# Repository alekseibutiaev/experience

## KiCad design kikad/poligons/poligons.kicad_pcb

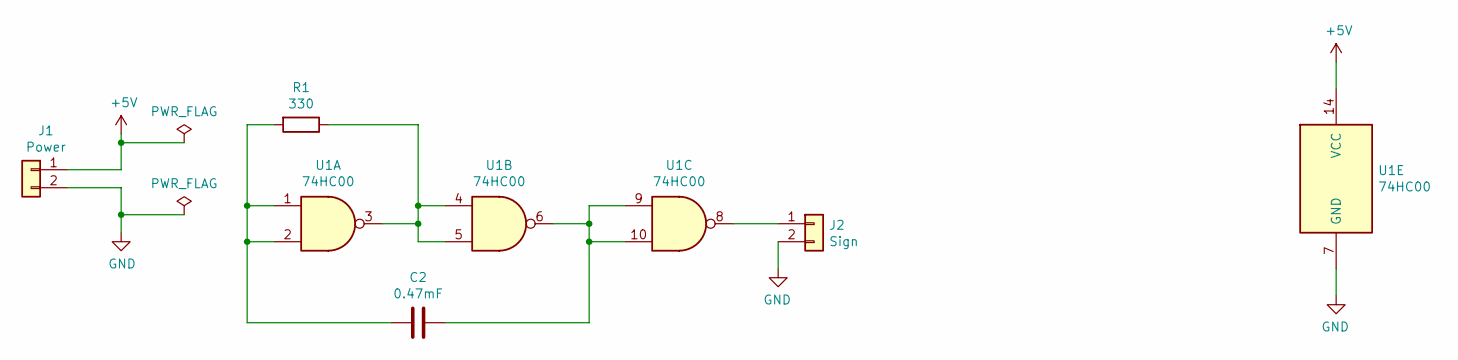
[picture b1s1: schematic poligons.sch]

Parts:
C2: 0.47mF; C_Axial_L3.8mm_D2.6mm_P7.50mm_Horizontal
J1: Power; PinHeader_1x02_P2.54mm_Vertical
J2: Sign; PinHeader_1x02_P2.54mm_Vertical
R1: 330; R_Axial_DIN0411_L9.9mm_D3.6mm_P15.24mm_Horizontal
U1: 74HC00; SO-14_3.9x8.65mm_P1.27mm

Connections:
+5V: J1.1, U1.14 (VCC)
GND: J1.2, J2.2, U1.7 (GND)
unnamed: C2.1, U1.6, U1.9, U1.10
unnamed: C2.2, R1.2, U1.1, U1.2
unnamed: J2.1, U1.8
unnamed: R1.1, U1.3, U1.4, U1.5

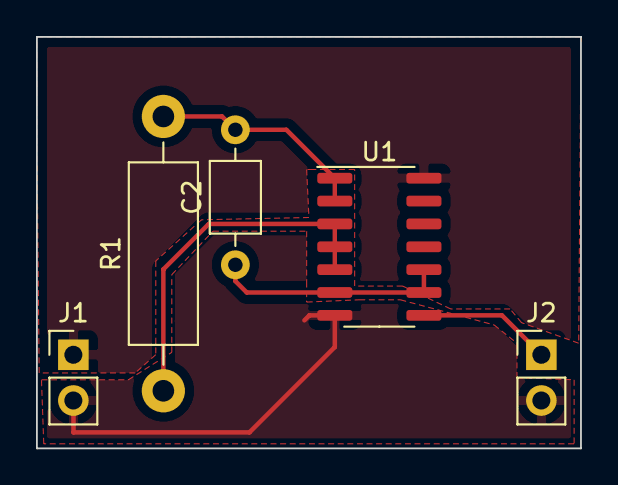
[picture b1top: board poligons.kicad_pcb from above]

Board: 2 copper layers, 30.2 x 22.9 mm, 5 parts (0 on the bottom side), 6 nets.

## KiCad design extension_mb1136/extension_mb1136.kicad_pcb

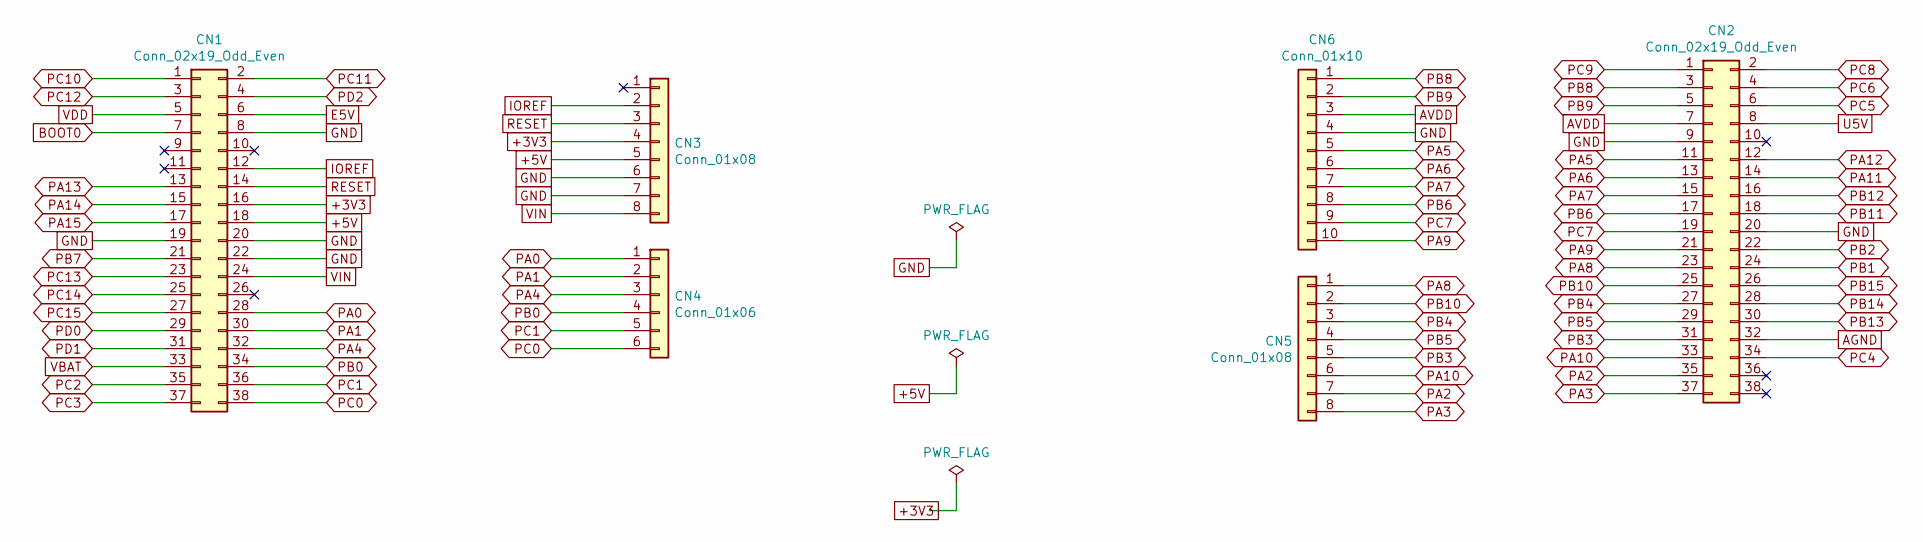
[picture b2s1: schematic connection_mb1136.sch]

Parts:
CN1, CN2: Conn_02x19_Odd_Even; PinHeader_2x19_P2.54mm_Vertical
CN3, CN5: Conn_01x08; PinSocket_1x08_P2.54mm_Vertical
CN4: Conn_01x06; PinSocket_1x06_P2.54mm_Vertical
CN6: Conn_01x10; PinSocket_1x10_P2.54mm_Vertical

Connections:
+3V3: CN1.16, CN3.4; also elsewhere on the board
+5V: CN1.18, CN3.5; also elsewhere on the board
AGND: CN2.32
AVDD: CN2.7, CN6.3
BOOT0: CN1.7
E5V: CN1.6
GND: CN1.8, CN1.19, CN1.20, CN1.22, CN2.9, CN2.20, CN3.6, CN3.7, CN6.4; also elsewhere on the board
IOREF: CN1.12, CN3.2
PA0: CN1.28, CN4.1
PA1: CN1.30, CN4.2
PA2: CN2.35, CN5.7
PA3: CN2.37, CN5.8
PA4: CN1.32, CN4.3
PA5: CN2.11, CN6.5
PA6: CN2.13, CN6.6
PA7: CN2.15, CN6.7
PA8: CN2.23, CN5.1
PA9: CN2.21, CN6.10; also elsewhere on the board
PA10: CN2.33, CN5.6
PA11: CN2.14; also elsewhere on the board
PA12: CN2.12; also elsewhere on the board
PA13: CN1.13
PA14: CN1.15
PA15: CN1.17
PB0: CN1.34, CN4.4
PB1: CN2.24
PB2: CN2.22
PB3: CN2.31, CN5.5
PB4: CN2.27, CN5.3
PB5: CN2.29, CN5.4
PB6: CN2.17, CN6.8
PB7: CN1.21
PB8: CN2.3, CN6.1
PB9: CN2.5, CN6.2
PB10: CN2.25, CN5.2; also elsewhere on the board
PB11: CN2.18
PB12: CN2.16
PB13: CN2.30
PB14: CN2.28
PB15: CN2.26
PC0: CN1.38, CN4.6
PC1: CN1.36, CN4.5
PC2: CN1.35
PC3: CN1.37
PC4: CN2.34
PC5: CN2.6
PC6: CN2.4
PC7: CN2.19, CN6.9
PC8: CN2.2; also elsewhere on the board
PC9: CN2.1; also elsewhere on the board
PC10: CN1.1
PC11: CN1.2
PC12: CN1.3
PC13: CN1.23
PC14: CN1.25
PC15: CN1.27
PD0: CN1.29
PD1: CN1.31
PD2: CN1.4
RESET: CN1.14, CN3.3
U5V: CN2.8
VBAT: CN1.33
VDD: CN1.5
VIN: CN1.24, CN3.8

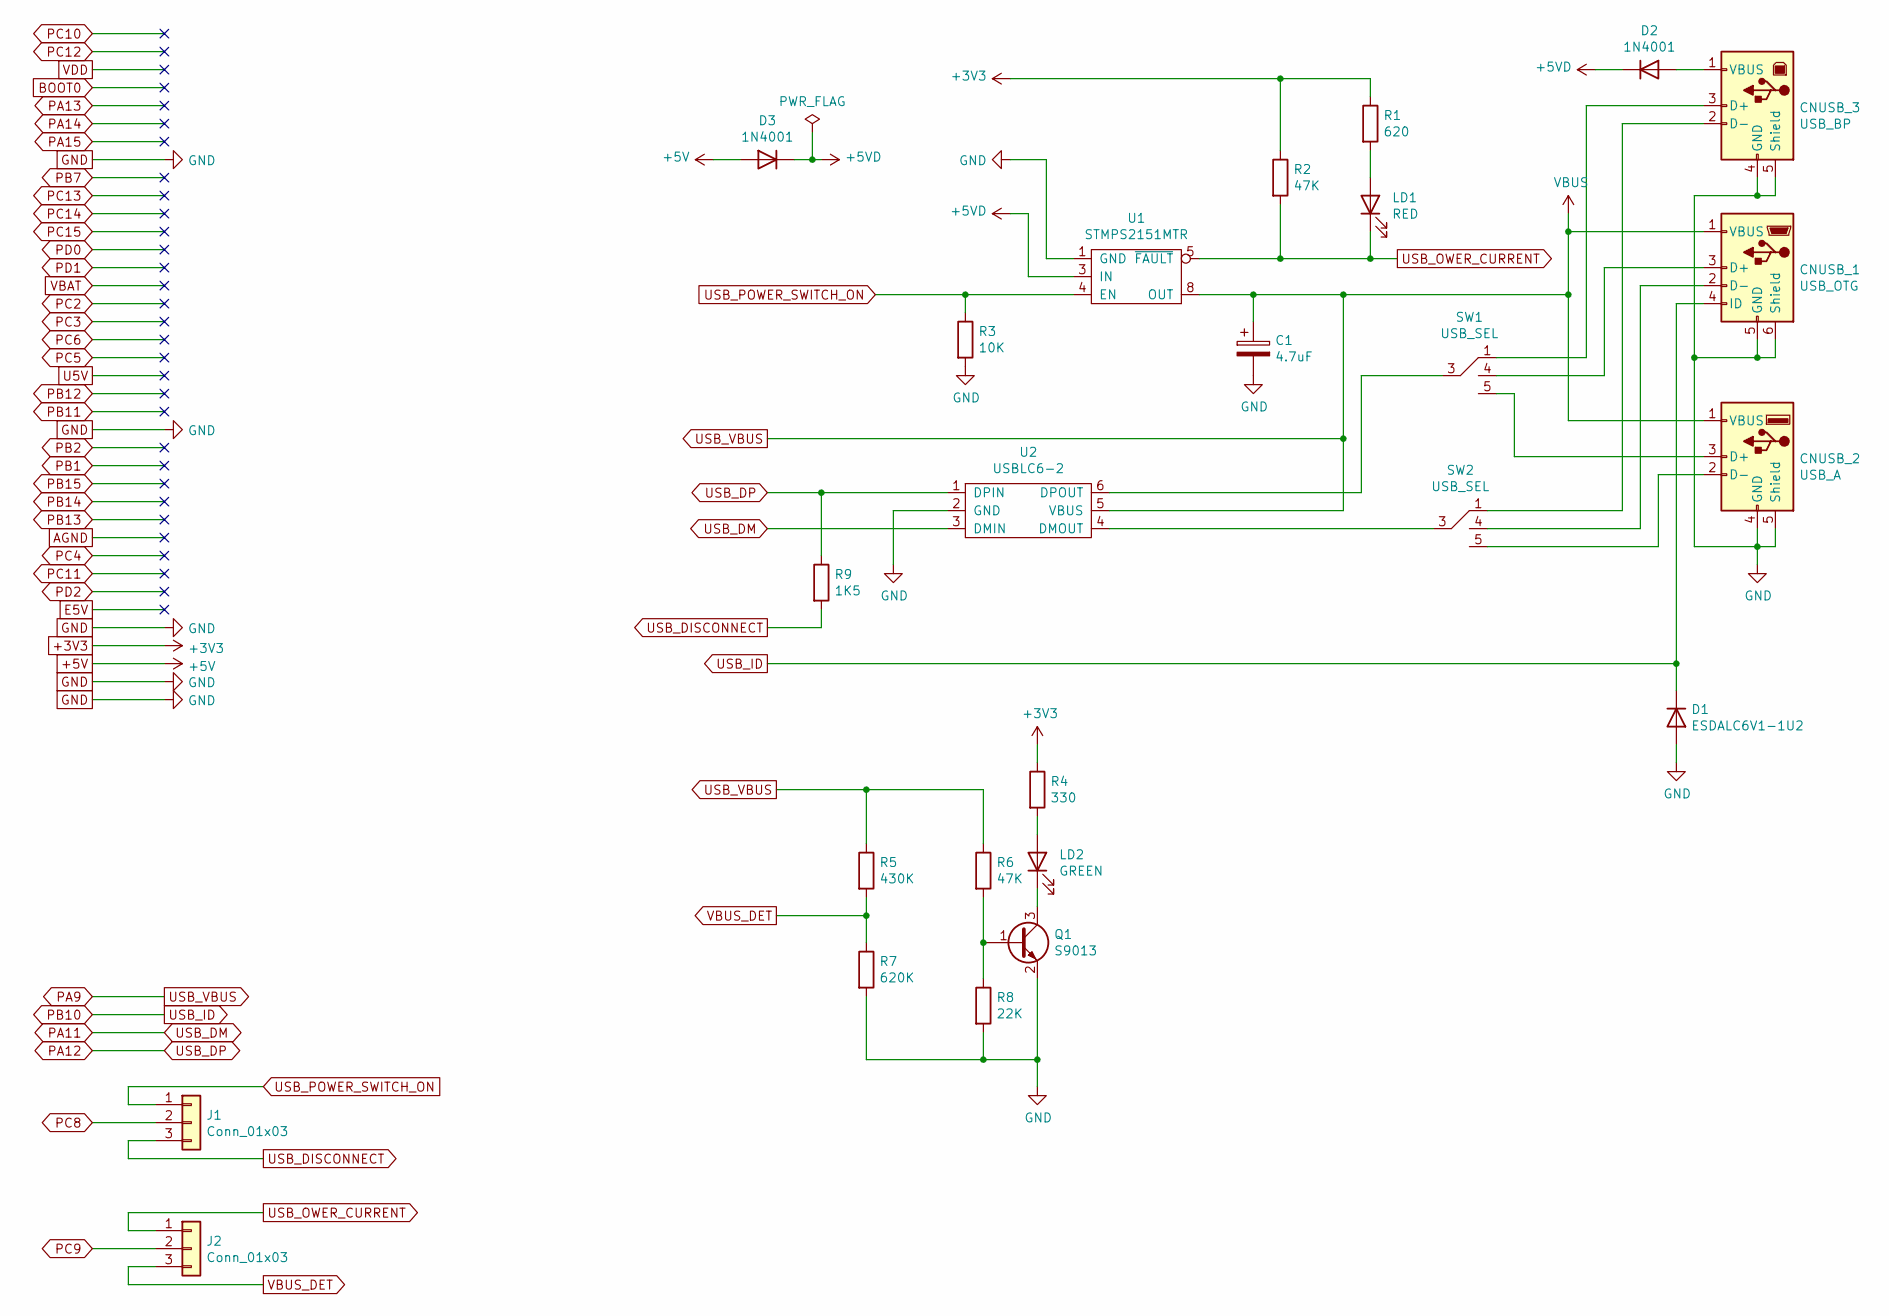
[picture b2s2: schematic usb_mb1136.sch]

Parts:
C1: 4.7uF; C_1206_3216Metric_Pad1.33x1.80mm_HandSolder
CNUSB_1: USB_OTG; USB_Micro-B_Molex-105017-0001
CNUSB_2: USB_A; USB_A_Molex_67643_Horizontal
CNUSB_3: USB_BP; USB_B_OST_USB-B1HSxx_Horizontal
D1: ESDALC6V1-1U2; D_0201_0603Metric
D2, D3: 1N4001; D_SOD-323_HandSoldering
J1, J2: Conn_01x03; PinHeader_1x03_P2.54mm_Vertical
LD1: RED; D_0805_2012Metric
LD2: GREEN; D_0805_2012Metric
Q1: S9013; SOT-23
R1: 620; R_0805_2012Metric
R2, R6: 47K; R_0805_2012Metric
R3: 10K; R_0805_2012Metric
R4: 330; R_0805_2012Metric
R5: 430K; R_0805_2012Metric
R7: 620K; R_0805_2012Metric
R8: 22K; R_0805_2012Metric
R9: 1K5; R_0805_2012Metric
SW1, SW2: USB_SEL; PinHeader_2x03_P2.54mm_Vertical
U1: STMPS2151MTR; SO-8_3.9x4.9mm_P1.27mm
U2: USBLC6-2; SOT-23-6_Handsoldering

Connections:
+3V3: R1.1, R2.1, R4.1; also elsewhere on the board
+5V: D3.2 (A); also elsewhere on the board
+5VD: D2.1 (K), D3.1 (K), U1.2 (IN), U1.3 (IN)
GND: C1.2, CNUSB_1.5 (GND), CNUSB_1.6 (Shield), CNUSB_2.4 (GND), CNUSB_2.5 (Shield), CNUSB_3.4 (GND), CNUSB_3.5 (Shield), D1.2 (A), Q1.2 (E), R3.2, R7.2, R8.2, U1.1 (GND), U2.2 (GND); also elsewhere on the board
unnamed: CNUSB_1.2 (D-), SW2.4
unnamed: CNUSB_1.3 (D+), SW1.4
unnamed: CNUSB_2.2 (D-), SW2.5
unnamed: CNUSB_2.3 (D+), SW1.5
unnamed: CNUSB_3.1 (VBUS), D2.2 (A)
unnamed: CNUSB_3.2 (D-), SW2.1
unnamed: CNUSB_3.3 (D+), SW1.1
unnamed: LD1.2 (A), R1.2
unnamed: LD2.1 (K), Q1.3 (C)
unnamed: LD2.2 (A), R4.2
unnamed: Q1.1 (B), R6.2, R8.1
unnamed: SW1.3, U2.6 (DPOUT)
unnamed: SW2.3, U2.4 (DMOUT)
PA9: C1.1, CNUSB_1.1 (VBUS), CNUSB_2.1 (VBUS), R5.1, R6.1, U1.6 (OUT), U1.7 (OUT), U1.8 (OUT), U2.5 (VBUS); also elsewhere on the board
PA11: U2.3 (DMIN); also elsewhere on the board
PA12: R9.1, U2.1 (DPIN); also elsewhere on the board
PB10: CNUSB_1.4 (ID), D1.1 (K); also elsewhere on the board
PC8: J1.2; also elsewhere on the board
PC9: J2.2; also elsewhere on the board
USB_DISCONNECT: J1.3, R9.2
USB_OWER_CURRENT: J2.1, LD1.1 (K), R2.2, U1.5 (~FAULT)
USB_POWER_SWITCH_ON: J1.1, R3.1, U1.4 (EN)
VBUS_DET: J2.3, R5.2, R7.1

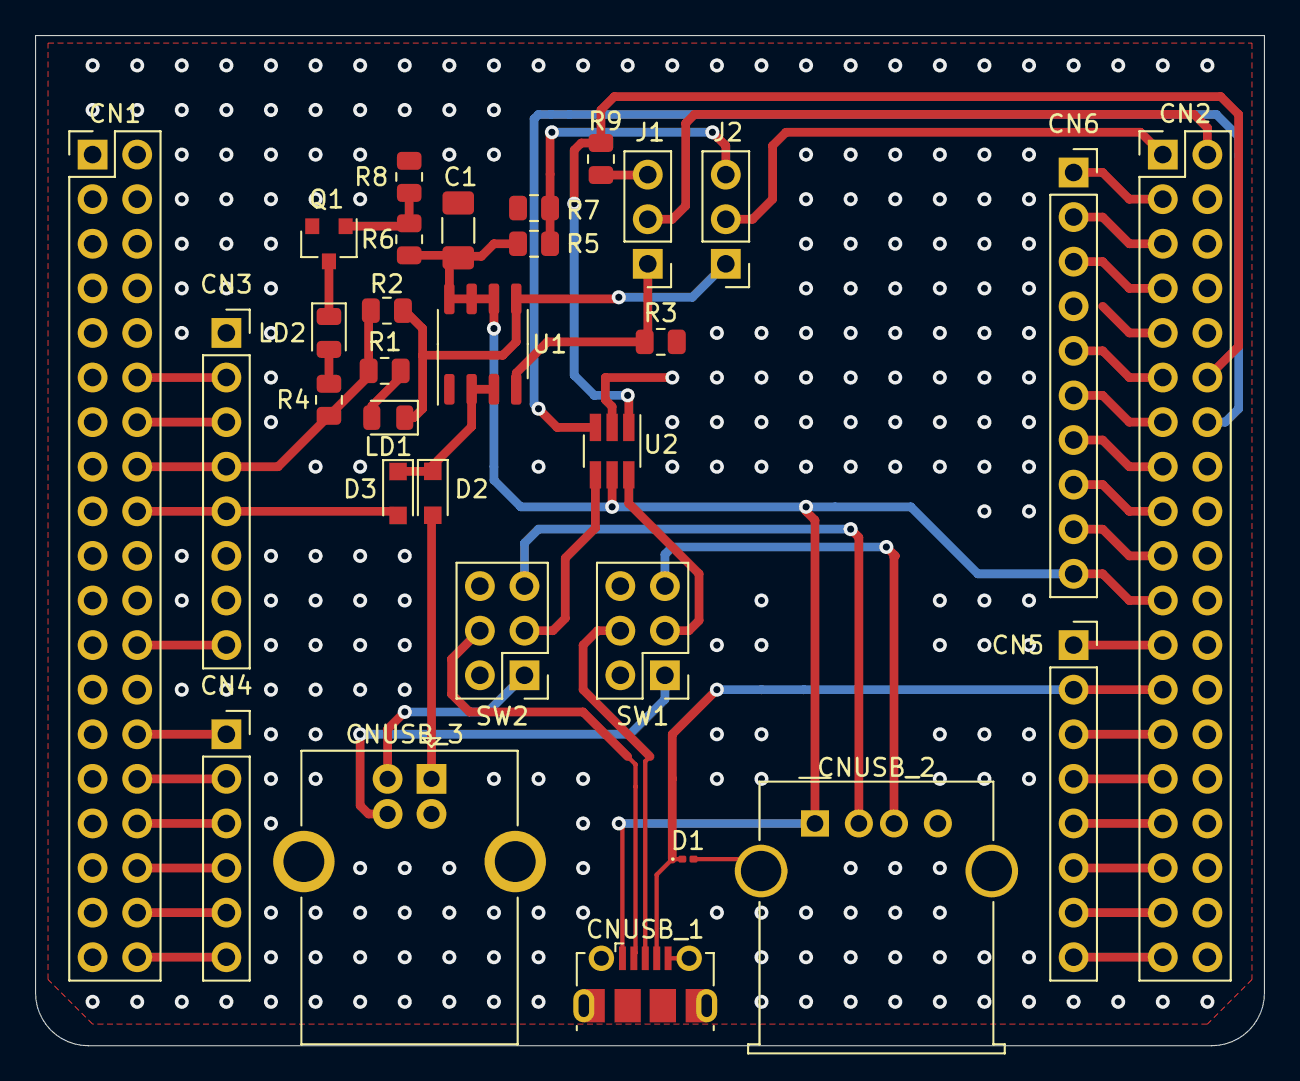
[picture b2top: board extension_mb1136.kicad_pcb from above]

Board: 2 copper layers, 70.0 x 57.5 mm, 31 parts (0 on the bottom side), 51 nets.

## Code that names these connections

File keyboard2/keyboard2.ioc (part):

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Mcu.UserName=STM32L476RGTx
PC9.GPIO_Label=USB_OWER_CURRENT
PC8.Signal=GPIO_Output
PA11.Mode=Host_Only
RCC.SYSCLKSource=RCC_SYSCLKSOURCE_PLLCLK
PC8.GPIO_Label=USB_POWER_SWITCH_ON
PA3.Mode=Asynchronous
PA9.Mode=Activate_VBUS
PA12.Signal=USB_OTG_FS_DP
PA9.Signal=USB_OTG_FS_VBUS
RCC.HSE_VALUE=8000000
board=custom
PC9.GPIO_PuPd=GPIO_NOPULL
PC9.GPIOParameters=GPIO_PuPd,GPIO_Label
Mcu.Name=STM32L476R(C-E-G)Tx
PA2.Signal=USART2_TX
PC8.GPIOParameters=GPIO_Label
RCC.SYSCLKFreq_VALUE=80000000
Mcu.Package=LQFP64
PA12.Mode=Host_Only
PA11.Signal=USB_OTG_FS_DM
PA2.Mode=Asynchronous
PC9.Signal=GPIO_Input
PA3.Signal=USART2_RX

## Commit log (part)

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2019-11-27 add connect function
2019-11-27 fix memory leack
2019-12-23 add fixgroup
2019-12-23 add option
2019-12-23 greate fixmsg
2019-12-23 fix header name
2019-12-23 msg creator
2019-12-24 fix prefix
2019-12-24 rename to table
2019-12-24 update tadle fix group range
2019-12-24 update table
2019-12-25 improve fix table
2019-12-26 improve factory, table
2019-12-26 add createtable.cpp
2019-12-26 create message cracker
2019-12-27 work copy
2019-12-27 improve xml parser
2019-12-27 some fixes
2019-12-27 non function changes
2019-12-27 rename pointer
2019-12-27 non functional changes
2020-01-24 some update
2020-01-27 improve wolker
2020-01-29 improve parser
2020-01-29 add type of field
2020-05-19 add gdb breakpoint exception example
2020-05-29 add boost-python-examples-master
2020-07-24 fix python version
2020-07-24 improve network
2020-07-24 improve common
2020-08-18 update network
2020-08-18 start cube project
2020-08-18 add cube
2020-10-13 Bump junit from 4.12 to 4.13.1 in /java/TCPIPServer
    Bumps [junit](https://github.com/junit-team/junit4) from 4.12 to 4.13.1.
    - [Release notes](https://github.com/junit-team/junit4/releases)
    - [Changelog](https://github.com/junit-team/junit4/blob/main/doc/ReleaseNotes4.12.md)
    - [Commits](https://github.com/junit-team/junit4/compare/r4.12...r4.13.1)
2020-10-24 add ZXKeyboard
2020-10-26 rename USART to USART2
2020-11-07 add keyboard project
2020-11-07 add system file
2020-11-07 Start keyboard
2020-11-26 add detach
2020-11-26 update ignore list
2020-11-26 add extension_mb1136
2020-11-26 add STMPS2151
2020-11-26 update schema
2020-11-26 USB_connector
2020-11-27 impruve schema
2020-11-27 update pin order
2020-11-27 add footprint
2020-11-29 add power flags
2020-11-29 add footprint mask
2020-11-29 undef "define us power symbol"
2020-11-29 replase U1 symbol
2020-11-30 start PCB
2020-12-15 add cmake scripts
2020-12-30 add poligons project
2020-12-30 add pcb
2021-01-08 add some cmake finder
2021-01-08 add some project
2021-01-08 update pid
2021-01-12 add connector, develop pcb
2021-01-12 update pcb
2021-01-13 restore number of element
2021-01-13 rename switch
2021-01-14 add file ignore list
2021-01-15 change footprint for D2,D3
2021-01-15 change footprint for SW1 SW2
2021-01-15 unfill all zone
2021-01-16 chande footprint for C1. update pcb
2021-01-22 improve echo server and client
2021-01-23 create schema
2021-01-23 add nucleo-32-MB1180
2021-01-23 add nucleo label
2021-01-23 move object
2021-01-24 improve tamplate
2021-01-24 add title
2021-01-31 restore extension_mb1136
2021-02-23 rename folder in template
2021-02-23 start new project
2021-02-23 add pthread
2021-02-23 modefied CMakeLists.txt
2021-02-23 implement timequote
2021-02-24 fix some problem
2021-02-25 use one second pwriod
2021-03-05 add ringbuf project
2021-03-05 modefied project
2021-03-05 fix error USB_DP
2021-03-06 Add Keyboard2 for MCU STM32L476RG
2021-03-06 Add some files
2021-03-06 Add Keboard for MCU STM32F107RC
2021-03-06 lg setting
2021-03-06 add Trace_Asynchronous_SW
2021-04-17 add extra file
2021-04-25 some changes
2021-04-26 Bump commons-io from 2.5 to 2.7 in /java/TCPIPServer
    Bumps commons-io from 2.5 to 2.7.
2021-05-01 add F107RC test
2021-05-01 modefied
2021-05-01 add launcher
2021-09-07 fix network for boost 1.71
2021-11-04 add tzbias
2021-11-05 improve tztime
2021-11-05 fix for modern gcc
2021-11-06 usb keyboard
2021-11-06 add enter zone to environment more improve
2021-11-08 add current time
2021-11-08 use boost
2021-11-11 modefies tzbias, add fixed
2021-11-19 add some code
2021-11-19 add fixlib
2021-12-02 fix for python 3
2021-12-03 14-MyEmbedding
2021-12-03 add 15-CallPython
2021-12-03 add finalize
2021-12-18 TestFile
2021-12-18 IgorTestProject
2021-12-20 add solor
2021-12-21 use c++-17 implement function get_light_direction, get_planet_point, get_solar_panel_normal
2021-12-21 fix some comments
2021-12-21 fix light direction to sun direction
2021-12-21 use constants object for identity matrix
2021-12-27 calculate angles
2021-12-27 fix day rotation period
2021-12-27 use glm::pi<float>() for pi use glm::identity<glm::mat4>() for identity
2022-01-13 add vecvsdec
2022-01-13 add coount
2022-01-14 add test
2022-01-18 add bpcond
2022-02-20 refactoring session,acceprot,connector
2022-02-20 use refactored library
2022-02-20 fix m_is_open flag add error information
2022-02-20 fix receive buffer problem move defalloc
2022-02-20 add launcher for client
2022-02-20 add file for local socket add method for select socket type
2022-02-21 update unix local socket
2022-02-22 fix signature of error_handle_t
2022-02-23 fix error message
2022-03-10 try modified connect
2022-03-10 try modified connect for unix local
2022-03-23 inprove library
2022-04-24 74XX library
2022-04-25 update library
2022-04-25 update library 74XX
2022-04-27 update 74xx library
2022-04-27 update script
2022-04-27 sort alias and add footprint
2022-04-27 update library 74IEX
2022-04-27 add tools
2022-04-27 update 74ICE library
2022-04-27 update library 74ICE
2022-05-20 Bump gson from 2.3.1 to 2.8.9 in /java/TCPIPServer
    Bumps [gson](https://github.com/google/gson) from 2.3.1 to 2.8.9.
    - [Release notes](https://github.com/google/gson/releases)
    - [Changelog](https://github.com/google/gson/blob/master/CHANGELOG.md)
    - [Commits](https://github.com/google/gson/compare/gson-2.3.1...gson-parent-2.8.9)
    ---
    updated-dependencies:
2022-05-28 move extension_mb1136 from experience to electronics
2022-08-05 add cmake variants
2022-08-06 add boost after 1.70
2022-08-18 use new codes for STM32F107 improve keyboard.
2022-08-18 improve keyboard
2022-08-18 add file
2022-08-26 add asio196
2022-08-26 improve for new boost
2022-09-06 start project karnaugh
2022-09-07 add some unit test
2022-10-27 sfda
2022-10-30 add interrupt project add release for keyboard3
2022-10-30 add KeyAddress scan
2022-10-30 gipo PC[0:4]
2022-11-11 add user led
2022-11-12 update keyboard
2022-11-14 change end of line
2022-11-14 use ony acribe bits for key data
2022-11-14 fix defenition
2022-11-15 refactoring
2022-11-15 add symbol shift
2022-11-15 without show buffer
2022-11-16 refactoring debug port
2022-11-17 change jtag to SWD
2022-11-17 change PC04 to PB04 add external interrupt for 0xFE request key
2022-11-17 add interrupt
2022-11-17 pull_up KeyRequest pin
2022-11-19 use 8bit for data bus
2022-11-19 some modeified
2022-11-19 restore PC0-4
2022-11-20 add freeRTOS and sdfat project delete interupt project keyboard3 try interrupt project
2022-11-22 rebuild project
2022-11-22 Some refactoring
2022-11-22 do not use sof vbus any more
2022-11-22 exclude from build stm32f1xx_hal_dma.c stm32f1xx_hal_flash_ex.c stm32f1xx_hal_flash.c stm32f1xx_hal_pwr.c stm32f1xx_hal_tim_ex.c stm32f1xx_hal_tim.c
2022-11-22 fix build flags
2022-11-22 implementation mouse
2022-11-23 add keyboard and mouse
2022-11-24 add zxkeys
2022-11-24 improve algorithm
2022-11-24 new algotithm
2022-11-24 improve test
2022-11-24 add bew algorithm
2022-11-26 add color pinout table
2022-11-26 fix color pin
2022-11-28 some updates
2022-11-28 spi geristors no waiting wariant
2022-11-28 add Load and Clear Signals
2022-12-15 fix hid callback
2022-12-31 start zxkeyboard project
2023-01-02 add cmake variants non functional changes pin CLEAR must by set main.c non functional changes select SPI MODE 2 use Register for key control
2023-01-02 fix button
2023-01-15 Fix jlink upload
2023-01-21 add different mcu supported
2023-01-21 update uart debug
2023-01-21 Add variant for debug nucleo board switch off run to main switch off cmake arguments add Documentation add external key
2023-01-21 use buffer for debug mode only
2023-01-22 add some comments
2023-01-23 Add zx keys
2023-04-25 add dfu example
2023-04-29 add improved dfu manager
2023-04-29 example dfu for f103rb
2023-04-29 fix start address
2023-04-29 use unix end of line
2023-04-29 fix print buffer
2023-05-04 add mass storage project
2023-05-14 fix keyboard
2023-05-19 add debug configuration
2023-05-19 Migrete to 1.8.5
2023-05-20 add st-link uploader
2023-05-20 add optimization by size
2023-05-20 non functional chamges
2023-07-07 add readmy.txt
2023-07-07 add test project for test jtag and swd connection
2023-07-08 add some file
2023-07-11 migrate to cubemx_6.9.0
2023-07-13 use usb_host v3.5.1
2023-08-12 add zx spectrum page test
2023-08-13 fix stack address
2023-08-19 add test ILI9341
2023-08-19 add config structure
2023-08-20 restore keqboard
2023-08-20 improve cmake file
2023-08-29 move jtag_f103rb to stm32-experirnce
2023-08-31 start ncds project
2023-09-04 update ncds
2023-10-03 some updare
2023-10-05 create confi class
2023-10-05 add changes
2023-10-05 improve library
2023-10-12 has connect and had shake
2023-10-18 improve
2023-10-25 update ignore mask
2023-10-25 add some test
2023-10-27 update libraries decode schematic
2024-04-16 improve config
2024-05-30 update information
2024-06-05 improve avrotest
2024-07-03 add schema
2024-07-05 add resource file
2024-07-05 max update
2024-07-05 add decoder
2024-07-09 deleted
2024-10-10 update code
2024-10-15 integrate in one exe file
2024-10-17 create avro devoder
2024-10-21 use change vector smart_ptr
2024-10-21 remove avro headers from interface
2024-10-21 some rename
2024-10-21 move all cobe to static library
2024-10-21 add schema callback
2024-10-30 improve avro decoder for integration
2024-11-01 more changes
2024-11-01 improve get_record
2024-11-04 use new rdkafka library update config use class for kafka logger
2024-11-04 add time point
2024-11-05 fix unused vairable
2024-11-06 add tread for consumer add queue for message add time stamp for message
2024-11-06 some refactorinf
2024-11-06 rename namespace from kf to nasdaq
2024-11-06 hide record
2024-11-06 fix sigseg
2024-11-07 restore pointers
2024-11-08 improve consumer
2024-11-08 fix compare void*
2024-11-11 add parametr list
2024-11-11 delete
2024-11-14 use multithread
2024-11-18 use external executer for consumer
2024-11-20 fix problem with update schematic multi thread
2024-11-21 use shared pointer for schema
2024-11-22 separated the connection and the logic of building the DOM
2024-11-26 add user data for callback modefied project builder
2024-11-26 use array vs condition set
2024-11-27 sintaxs improve
2024-11-27 move vallue type to top level
2024-11-27 improve sources tree
2024-12-04 more refactoring
2024-12-04 update messages
2024-12-06 improve unit test
2024-12-11 update message
2024-12-11 add sequence for messaage add message for dom
2025-01-31 use new cmake format for library use link for more cleary
2025-02-28 improve ignore
2025-02-28 restore sn
2025-03-20 add unit test
2025-03-24 improve serial number
2025-03-25 merge
2025-03-27 impruve
2025-04-01 add marking for first message
2025-04-01 start equence_manager
2025-04-02 tename dom to tw
2025-04-04 some fix
2025-04-08 update msg
2025-04-09 add sequence
2026-01-07 recreate rep
2026-01-07 update ignore
2026-01-07 add test code
2026-01-08 add iterator concept test
